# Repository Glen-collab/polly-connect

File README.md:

# 🦜 Polly Connect

**ESP32-based voice assistant for garage/workshop storage management**

Tell Polly where you put things, ask her later. Simple as that.

```
"Hey Polly, the wrench is in the left drawer"
    ... later ...
"Hey Polly, where's my wrench?"
    → "The wrench is in the left drawer"
```

## Architecture

```
┌─────────────────┐         ┌─────────────────┐
│   ESP32 Device  │  WiFi   │   Cloud Server  │
│   (Ears/Mouth)  │◄───────►│    (Brain)      │
│                 │         │                 │
│ • Wake word     │         │ • Whisper STT   │
│ • Audio capture │         │ • Intent parse  │
│ • Audio output  │         │ • Database      │
└─────────────────┘         │ • TTS           │
                            └─────────────────┘
```

**ESP32** handles audio I/O and wake word detection.  
**Server** handles the "smarts" — transcription, understanding, responses.

## Hardware Requirements

| Part | Purpose | ~Price |
|------|---------|--------|
| ESP32-WROOM-32 | Microcontroller | $6 |
| INMP441 | I2S Microphone | $3 |
| MAX98357A | I2S Amplifier | $4 |
| Small Speaker | Audio output | $3 |

**Total: ~$16-20** (vs $100+ for Raspberry Pi build)

## Quick Start

### 1. Server Setup

```bash
cd server

# Create virtual environment
python -m venv venv
source venv/bin/activate  # or `venv\Scripts\activate` on Windows

# Install dependencies
pip install -r requirements.txt

# Run server
python main.py
```

Server runs at `http://localhost:8000`

### 2. ESP32 Setup

1. Install [Arduino IDE](https://www.arduino.cc/en/software)
2. Add ESP32 board support (see [docs/wiring.md](docs/wiring.md))
3. Install libraries:
   - WebSocketsClient
   - ArduinoJson
   - Base64
4. Edit `firmware/polly-esp32/config.h`:
   ```cpp
   #define WIFI_SSID     "your_wifi"
   #define WIFI_PASSWORD "your_password"
   #define SERVER_HOST   "192.168.1.100"  // Your server IP
   ```
5. Upload to ESP32

### 3. Wire It Up

See [docs/wiring.md](docs/wiring.md) for detailed pinout.

Quick reference:
```
INMP441 Mic → ESP32          MAX98357A Amp → ESP32
-----------   -----          -------------   -----
VDD → 3.3V                   VIN → 5V
GND → GND                    GND → GND
SD  → GPIO32                 DIN → GPIO22
WS  → GPIO25                 BCLK → GPIO26
SCK → GPIO33                 LRC → GPIO21
L/R → GND
```

### 4. Test It

1. Open Serial Monitor (115200 baud)
2. Press 'r' to start recording (wake word coming in Phase 4)
3. Speak: "The hammer is on the pegboard"
4. Listen for response

## Project Structure

```
polly-connect/
├── server/                 # Cloud brain (Python/FastAPI)
│   ├── api/                # REST and WebSocket endpoints
│   ├── core/               # Business logic
│   │   ├── intent_parser.py    # NLP command parsing
│   │   ├── database.py         # SQLite storage
│   │   ├── transcription.py    # Whisper STT
│   │   └── tts.py              # Text-to-speech
│   └── main.py             # Entry point
│
├── firmware/               # ESP32 code (Arduino)
│   └── polly-esp32/
│       ├── polly-esp32.ino     # Main sketch
│       ├── config.h            # Configuration
│       ├── audio_capture.h     # Mic driver
│       └── audio_playback.h    # Speaker driver
│
├── wake-word/              # Wake word training assets
│   ├── positive/           # "Hey Polly" samples
│   └── negative/           # Non-wake-word samples
│
└── docs/                   # Documentation
    ├── architecture.md
    ├── wiring.md
    └── api.md
```

## Build Phases

- [x] **Phase 1:** Hardware test (mic + speaker working)
- [ ] **Phase 2:** WiFi streaming (ESP32 → Server)
- [ ] **Phase 3:** Cloud brain (Whisper + intent + TTS)
- [ ] **Phase 4:** Wake word ("Hey Polly")
- [ ] **Phase 5:** Optimization (latency, silence detection)

## Voice Commands

| You say... | Polly does... |
|------------|---------------|
| "The hammer is on the pegboard" | Stores location |
| "Where is the hammer?" | Retrieves location |
| "What's in the red bin?" | Lists items in location |
| "Forget the old screwdriver" | Deletes item |
| "List everything" | Shows all items |

## API

REST API available at `http://localhost:8000/api/`:

```bash
# Natural language command
curl -X POST http://localhost:8000/api/command \
  -H "Content-Type: application/json" \
  -d '{"text": "where is the wrench"}'

# List all items
curl http://localhost:8000/api/items

# Get stats
curl http://localhost:8000/api/stats
```

See [docs/api.md](docs/api.md) for full reference.

## Roadmap

### Polly CONNECT (this repo)
- [x] ESP32 + cloud architecture
- [ ] Full voice pipeline
- [ ] Web dashboard
- [ ] Multi-device support
- [ ] User accounts

### Polly LOCAL (future)
- [ ] Fully offline ESP32-S3 version
- [ ] Limited command vocabulary
- [ ] No cloud required
- [ ] ~$25 total cost

## Credits

Ported from [The Parrot](https://github.com/Glen-collab/parrot) - original Raspberry Pi version.

## License

MIT - Do whatever you want with it.

---

Made for messy garages everywhere. 🔧

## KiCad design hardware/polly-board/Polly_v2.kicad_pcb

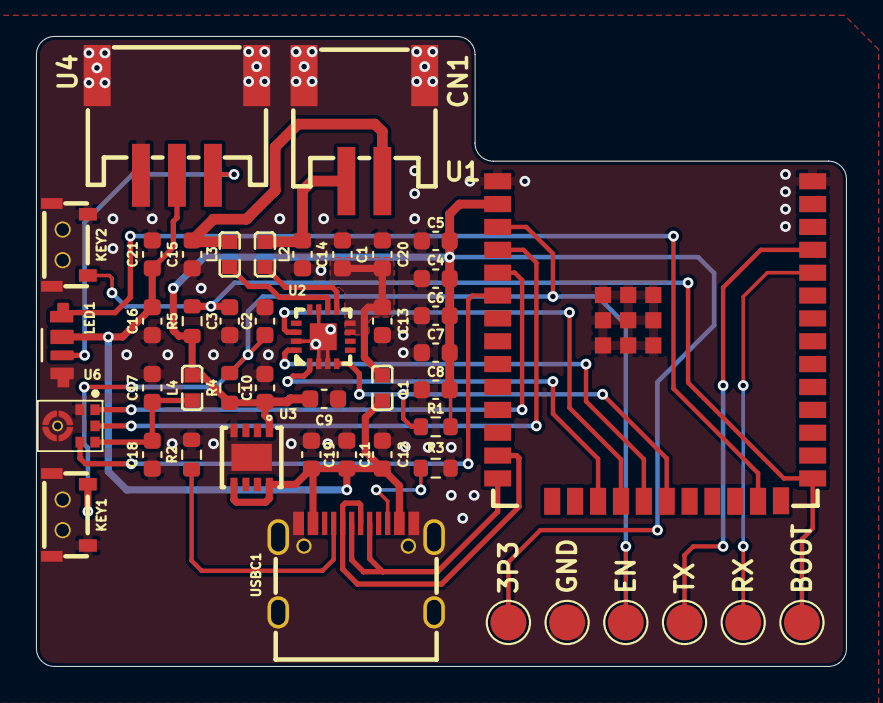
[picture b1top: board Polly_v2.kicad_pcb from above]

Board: 2 copper layers, 45.0 x 35.0 mm, 46 parts (0 on the bottom side), 26 nets.

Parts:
C1, C20: 4.7uF; C_0603_1608Metric
C2, C3, C4, C5, C10, C12, C13, C18, C21: 100nF; C_0603_1608Metric
C6, C7, C8, C9, C11, C17, C19: 10uF; C_0603_1608Metric
C14, C15: 470pF; C_0603_1608Metric
C16: 1uF; C_0603_1608Metric
CN1: S2B-PH-SM4-TB; CONN-SMD_P2.00_S2B-PH-SM4-TB-LF-SN
KEY1, KEY2: SW2; KEY-SMD_1TS003B-2500-3500A-CT
L1, L2, L3, L4: 120Ω@100MHz; L0603
LED1: SK6812SIDE-A-RVS; LED-SMD_4P-L4.0-W1.6-L
R1: 100k; R_0603_1608Metric
R2, R3: 5.1k; R_0603_1608Metric
R4, R5: 10k; R_0603_1608Metric
TP1, TP2, TP3, TP4, TP5, TP6: TestPoint; TestPoint_Pad_D2.0mm
U1: ESP32-S3-WROOM-1; WIRELM-SMD_ESP32-S3-WROOM-1
U2: MAX98357AETE+T; TQFN-16_L3.0-W3.0-P0.50-BL-EP1.5
U3: AP7361-33FGE-7; U-DFN3030-8_L3.0-W3.0-P0.65-BL-EP
U4: S3B-PH-SM4-TB; CONN-SMD_S3B-PH-SM4-TB-LF-SN
U6: ICS-43434_C5656610; MIC-SMD_6P-L3.5-W2.7-P0.90-BL
USBC1: TYPE-C-31-M-12; USB-C_SMD-TYPE-C-31-M-12_1

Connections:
+ESP_3P3: C4.2, C5.2, C6.2, C7.2, C8.2, C9.2, C10.2, L4.1, R1.1, R4.1, R5.1, TP2.1, U1.2 (3V3), U3.1 (OUT)
+MIC_3P3: C17.2, C18.2, L4.2, U6.5 (VDD)
+SP_5P0: C1.2, C13.2, C20.2, L1.2, U2.7 (VDD), U2.8 (VDD)
+USB_5P0: C11.2, C12.2, C16.2, C19.2, C21.2, L1.1, LED1.2 (VDD), U3.5 (EN), U3.8 (IN), U4.2, USBC1.A4B9 (VBUS), USBC1.B4A9 (VBUS)
/ESP_BOOT: C3.1, KEY2.2, R5.2, TP4.1, U1.27 (IO0)
/ESP_EN: C2.1, KEY1.1, R4.2, TP3.1, U1.3 (EN)
/ESP_IO4: U1.4 (IO4), U6.6 (SD)
/ESP_IO5: U1.5 (IO5), U6.1 (WS)
/ESP_IO6: U1.6 (IO6), U6.4 (SCK)
/ESP_IO10: U1.18 (IO10), U2.1 (DIN)
/ESP_IO11: U1.19 (IO11), U2.14 (LRCLK)
/ESP_IO12: U1.20 (IO12), U2.16 (BCLK)
/ESP_IO13: R1.2, U1.21 (IO13), U2.4 (~SD_MODE)
/ESP_IO19: U1.13 (IO19), USBC1.A7 (DN1), USBC1.B7 (DN2)
/ESP_IO20: U1.14 (IO20), USBC1.A6 (DP1), USBC1.B6 (DP2)
/ESP_IO48: LED1.1 (DIN), U1.25 (IO48)
/ESP_RXD0: TP6.1, U1.36 (RXD0)
/ESP_TXD0: TP5.1, U1.37 (TXD0)
GND: C1.1, C2.2, C3.2, C4.1, C5.1, C6.1, C7.1, C8.1, C9.1, C10.1, C11.1, C12.1, C13.1, C14.1, C15.1, C16.1, C17.1, C18.1, C19.1, C20.1, C21.1, CN1.MP, KEY1.0, KEY1.2, KEY2.1, KEY2.MP, LED1.4 (GND), R2.2, R3.2, TP1.1, U1.1 (GND), U1.40 (GND), U1.41 (GND), U2.2 (GAIN_SLOT), U2.3 (GND), U2.11 (GND), U2.15 (GND), U2.17 (EP), U3.4 (GND), U3.9 (GND), U4.3, U4.MP, U6.2 (LR), U6.3 (GND), USBC1.1 (EH), USBC1.2 (EH), USBC1.3 (EH), USBC1.4 (EH), USBC1.A1B12 (GND), USBC1.B1A12 (GND)
unnamed: C14.2, CN1.2, L2.2
unnamed: C15.2, CN1.1, L3.2
unnamed: LED1.3 (DOUT), U4.1
unnamed: L3.1, U2.10 (OUTN)
unnamed: L2.1, U2.9 (OUTP)
unnamed: R2.1, USBC1.A5 (CC1)
unnamed: R3.1, USBC1.B5 (CC2)

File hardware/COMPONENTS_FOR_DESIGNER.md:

# Polly PCB v2 — Canonical Spec

**Source of truth:** `hardware/polly-board/Polly_v2.*` — the KiCad project Paul P. (Upwork) delivered in April 2026.
The schematic, BOM, CPL, and gerbers there are what gets manufactured. This document explains the choices and the
non-negotiable details so a new designer can review or extend the board without re-litigating decisions.

**Board:** 45 × 35 mm, 2-layer FR4, fully SMT-assembled by JLCPCB.

**End-user connections (only these are customer-facing):**
- USB-C (power + firmware flash)
- JST-PH 2-pin SMD (speaker wire out)
- JST-PH 3-pin SMD (LED chain to Polly's eyes)

No exposed pin headers. No hand soldering. UART fallback exposed as **labeled SMD test pads along the bottom edge**
(pogo-pin probe, not a connector).

---

## BOM (Paul's v2, manufactured by JLCPCB)

All part numbers are JLCPCB LCSC codes. Verify stock right before ordering — LCSC parts rotate in and out.

| Ref | Component | LCSC | Package | Notes |
|-----|-----------|------|---------|-------|
| U1 | **ESP32-S3-WROOM-1-N16R8** | **C2913202** | SMD module | **DO NOT SUBSTITUTE.** Must be N16R8 (16 MB flash, 8 MB octal PSRAM). A previous order was substituted to N4R2, which is incompatible with the firmware. Add this as a human-readable order note to JLCPCB. |
| U2 | MAX98357AETE+T | C910544 | TQFN-16 (3×3 mm) | I2S mono audio amp. Runs on **+5V (SP_5V)** for max volume — do NOT tie VDD to +3.3V. **GAIN_SLOT tied to GND = 15 dB (loudest setting).** **SD_MODE controlled by GPIO13** (firmware drives high to enable amp, low to mute — saves power and kills idle hiss). |
| U3 | AP7361-33FGE-7 | C460392 | DFN-8 | 5V → 3.3V LDO regulator, 1 A capability, low noise. Replaces AMS1117 from the v1 spec — better part for clean audio rails. |
| U6 | **ICS-43434** (TDK, I2S MEMS mic) | **C5656610** | LGA-6 | I2S MEMS mic. Replaces MSM261DGT003 (PDM, incompatible with firmware) and INMP441 (out of stock at JLCPCB). 3.3V only (5V will damage the part). |
| LED1 | **SK6812SIDE-A-RVS** | **C2890037** | SMD 4P, side-emit reverse-mount | Addressable RGB, side-firing through a window in the perch / stump wall. Same one-wire 800 kHz protocol as WS2812 — firmware works unchanged. **No series resistor on the data line** (direct GPIO48 → DIN). DOUT chains off-board through the LED-eyes JST. |
| USBC1 | USB-C receptacle (16-pin) | C165948 | TYPE-C-31-M-12 | Power + USB 2.0 data. Place on the **bottom edge** of the board. |
| CN1 | JST-PH 2-pin SMD (speaker out) | **C295747** | S2B-PH-SM4-TB, 2.0 mm pitch, side-entry SMD | Pin 1 = OUTP, Pin 2 = OUTN. SMD = no through-hole soldering at JLCPCB. |
| U4 | JST-PH 3-pin SMD (LED eyes out) | **C265101** | S3B-PH-SM4-TB, 2.0 mm pitch, side-entry SMD | **Pin 1 = DATA (chain-out from LED1 DOUT), Pin 2 = +5V, Pin 3 = GND.** Customer pigtails MUST match this pin order — DATA is on pin 1, not the middle pin. |
| KEY1 | **RESET button** | C255810 | SMD tactile (1TS003B-2500-3500A-CT) | EN → GND when pressed. |
| KEY2 | **BOOT / Story button** | C255810 | SMD tactile (1TS003B-2500-3500A-CT) | GPIO0 → GND when pressed. Doubles as Story button in firmware (short press = record, hold on power-up = flash mode). |

**Passives (all 0603):**

| Ref | Value | LCSC | Purpose |
|-----|-------|------|---------|
| C1, C20 | 4.7 µF | C69335 | USB_5V / SP_5V bulk |
| C10, C12, C13, C18, C2, C21, C3, C4, C5 | 100 nF | C1590 | Decoupling across rails (ESP32, LDO, amp, mic) — including **C2 100nF on EN-to-GND** (RC reset filter) and **C3 100nF on BOOT-to-GND** (debounce) |
| C11, C17, C19, C6, C7, C8, C9 | 10 µF | C70225 | Bulk caps on 3.3V rails and USB VBUS |
| C14, C15 | 470 pF | C1620 | Class-D speaker output EMI filter (paired with L2/L3) |
| C16 | 1 µF | C1592 | LED chain bulk |
| L1, L2, L3, L4 | 120 Ω @ 100 MHz | C14709 | Ferrite beads — **L1 splits USB_5V from SP_5V** (audio gets clean 5V), **L2/L3 on speaker outputs** (Class-D filter), **L4 splits ESP_3V3 from MIC_3V3** (clean mic supply) |
| R1 | 100 kΩ | C14675 | MAX98357A SD_MODE pull-up to GPIO13 |
| R2, R3 | 5.1 kΩ | C14677 | USB-C CC1 / CC2 pull-**downs to GND** |
| R4, R5 | 10 kΩ | C15401 | EN pull-up + BOOT pull-up to +3.3V |

---

## GPIO Pin Assignments (firmware-locked — DO NOT CHANGE)

| GPIO | Function | Connected to |
|------|----------|-------------|
| GPIO0 | BOOT / Story button | KEY2 → GND |
| GPIO4 | Mic SD (I2S data) | U6 SD |
| GPIO5 | Mic WS (I2S word select) | U6 WS |
| GPIO6 | Mic SCK (I2S clock) | U6 SCK |
| GPIO10 | Amp DIN | U2 DIN |
| GPIO11 | Amp LRCLK | U2 LRCLK |
| GPIO12 | Amp BCLK | U2 BCLK |
| **GPIO13** | **Amp SD_MODE (software enable)** | U2 SD_MODE via R1 100k. Firmware must drive HIGH at boot to enable the amp. |
| GPIO19 | USB D- | USBC1 D- |
| GPIO20 | USB D+ | USBC1 D+ |
| GPIO48 | RGB LED data | LED1 DIN |
| EN | Reset | R4 pull-up + KEY1 → GND, with C2 100nF RC filter |

All other GPIOs left floating.

---

## Layout Rules (must match)

See `polly-board/polly_board_v2_final.png` for the visual reference.

1. **Board size: 45 × 35 mm**, 2-layer.
2. **Perch edge** (the edge that faces outward through the 3D-printed stump wall) carries all user-facing components:
   - Left to right: **KEY1 (Reset) — LED1 — U6 (Mic) — KEY2 (Story/BOOT)**
   - **Minimum 15 mm between KEY1 and KEY2** (button cap clearance, ergonomic press)
   - Mic acoustic port faces outward sideways, not down through the PCB
   - LED side-firing through a window in the stump
   - All four components flush with or within 1 mm of the Edge.Cuts boundary
3. **Bottom edge** carries USB-C and six labeled SMD test pads: **3P3, GND, EN, TX, RX, BOOT** (for UART-based firmware recovery via pogo pins).
4. **JSTs (CN1 speaker, U4 LED eyes)** on a non-perch edge — top or back. Wires route internally.
5. **Mic ↔ speaker JST** kept as far apart as the board allows, to reduce acoustic feedback.
6. **ESP32 PCB antenna** overhangs board edge OR has no ground pour / no copper directly beneath it.

---

## Non-negotiable electrical details (don't repeat past mistakes)

- **CC1 and CC2**: 5.1 **kΩ** (NOT 5.1 Ω) pull-**down** to GND (NOT pull-up to 3.3V). USB-C host will refuse to supply power otherwise.
- **USB D+ = GPIO20, USB D- = GPIO19** (native USB).
- **KEY1 (RESET) on EN**, **KEY2 (BOOT) on GPIO0**.
- **R4 (EN pull-up) tied to EN pin** + **C2 100nF on EN-to-GND** for clean reset.
- **ICS-43434 VDD = +3.3V only**. +5V damages it.
- **MAX98357A VDD = +5V (SP_5V via L1 ferrite bead from VBUS)**, NOT +3.3V (quieter at 3.3V).
- **MAX98357A GAIN_SLOT = GND** for 15 dB max gain.
- **MAX98357A SD_MODE = GPIO13 via R1 100k** — firmware must drive HIGH at boot.
- **WS2812 / SK6812 data line direct from GPIO48** — no series resistor.
- **ESP32 module 3V3 pin → +ESP_3P3, GND pins → GND**. Not swapped.
- **Ground pour on both layers**, connected by vias, clear of antenna area.

---

## What to deliver

1. KiCad project (`.kicad_pro`, `.kicad_sch`, `.kicad_pcb`) — already committed at `hardware/polly-board/Polly_v2.*`
2. JLCPCB-ready gerbers (zip) — already at `hardware/polly-board/production/Polly_V2.zip`
3. BOM CSV in LCSC format (`Designator, Footprint, Quantity, Value, LCSC Part #`) — at `hardware/polly-board/production/Polly_V2_bom.csv`
4. CPL / POS CSV (`Designator, Mid X, Mid Y, Rotation, Layer`) — at `hardware/polly-board/production/Polly_V2_positions.csv`

Order quantity: **5–10 prototypes first** for validation before any production run.

---

## Alternate designs in flight

- **Paul P. (Upwork) — `hardware/polly-board/`** — current canonical, manufactured-ready.
- **Fiverr designer (alt) — `hardware/polly-board-alt-fiverr/`** — alternate v2 layout being developed in parallel as a price/quality comparison. Glen plans to assemble both and bench-test before locking in a single design for production.

If you're a new designer joining the project, **start from Paul's files**. If asked to do an "alt" version, copy his project as your starting reference rather than redrawing from scratch.

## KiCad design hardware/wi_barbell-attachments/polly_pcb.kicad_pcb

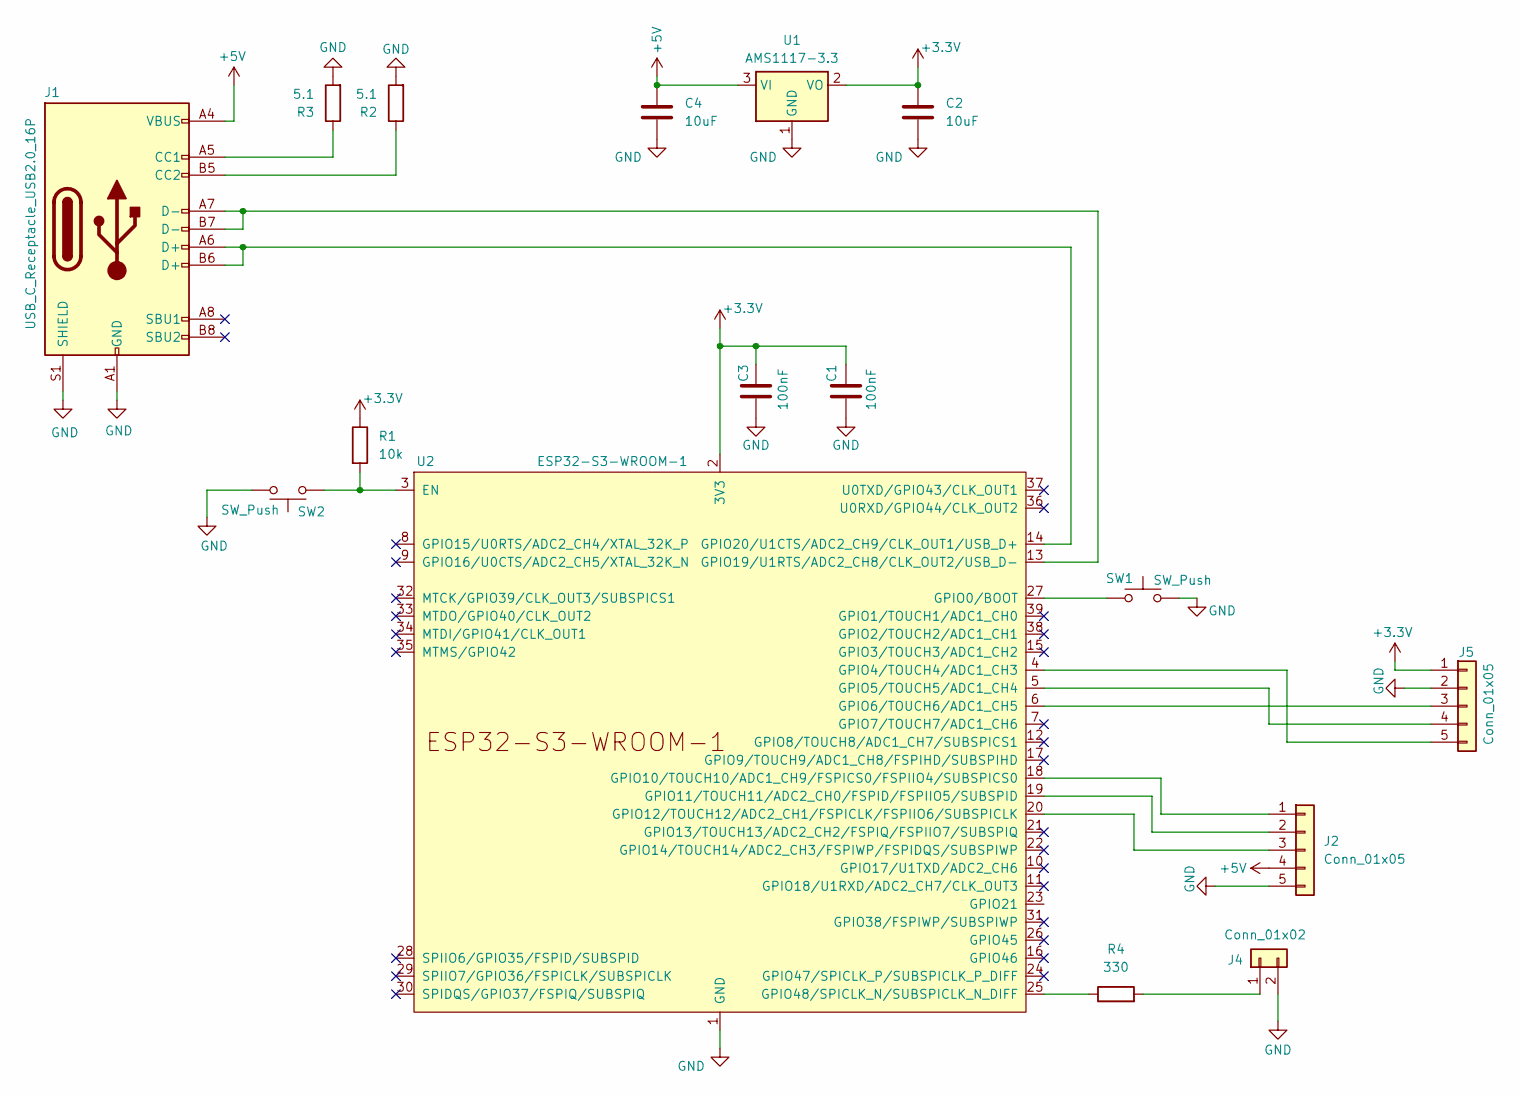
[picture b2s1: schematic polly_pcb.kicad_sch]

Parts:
C1, C3: 100nF; C_0805_2012Metric
C2, C4: 10uF; C_0805_2012Metric
J1: USB_C_Receptacle_USB2.0_16P; USB_C_Receptacle_HRO_TYPE-C-31-M-12
J2, J5: Conn_01x05; PinHeader_1x05_P2.54mm_Vertical
J4: Conn_01x02; PinHeader_1x02_P2.54mm_Vertical
R1: 10k; R_0805_2012Metric
R2, R3: 5.1; R_0805_2012Metric
R4: 330; R_0805_2012Metric
SW1, SW2: SW_Push; SW_SPST_PTS645Sx43SMTR92
U1: AMS1117-3.3; SOT-223-3_TabPin2
U2: ESP32-S3-WROOM-1

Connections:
+3.3V: C1.1, C2.1, C3.1, J5.1, R1.1, U1.2 (VO), U2.2 (3V3)
+5V: C4.1, J1.A4 (VBUS), J1.A9 (VBUS), J1.B4 (VBUS), J1.B9 (VBUS), J2.4, U1.3 (VI)
GND: C1.2, C2.2, C3.2, C4.2, J1.A1 (GND), J1.A12 (GND), J1.B1 (GND), J1.B12 (GND), J1.S1 (SHIELD), J2.5, J4.2, J5.2, R2.2, R3.2, SW1.2, SW2.2, U1.1 (GND), U2.1 (GND), U2.40 (GND), U2.41 (GND)
unnamed: J1.A5 (CC1), R3.1
unnamed: J1.B5 (CC2), R2.1
unnamed: J2.1, U2.18 (GPIO10/TOUCH10/ADC1_CH9/FSPICS0/FSPIIO4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)
unnamed: J2.2, U2.19 (GPIO11/TOUCH11/ADC2_CH0/FSPID/FSPIIO5/S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)
unnamed: J2.3, U2.20 (GPIO12/TOUCH12/ADC2_CH1/FSPICLK/FSPIIO6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)
unnamed: J4.1, R4.2
unnamed: J5.3, U2.6 (GPIO6/TOUCH6/ADC1_CH5)
unnamed: J5.4, U2.5 (GPIO5/TOUCH5/ADC1_CH4)
unnamed: J5.5, U2.4 (GPIO4/TOUCH4/ADC1_CH3)
unnamed: R1.2, SW2.1, U2.3 (EN)
unnamed: SW1.1, U2.27 (GPIO0/BOOT)
unnamed: J1.A7 (D-), J1.B7 (D-), U2.13 (GPIO19/U1RTS/ADC2_CH8/CLK_OUT2/USB_D-)
unnamed: J1.A6 (D+), J1.B6 (D+), U2.14 (GPIO20/U1CTS/ADC2_CH9/CLK_OUT1/USB_D+)
unnamed: R4.1, U2.25 (GPIO48/SPICLK_N/SUBSPICLK_N_DIFF)

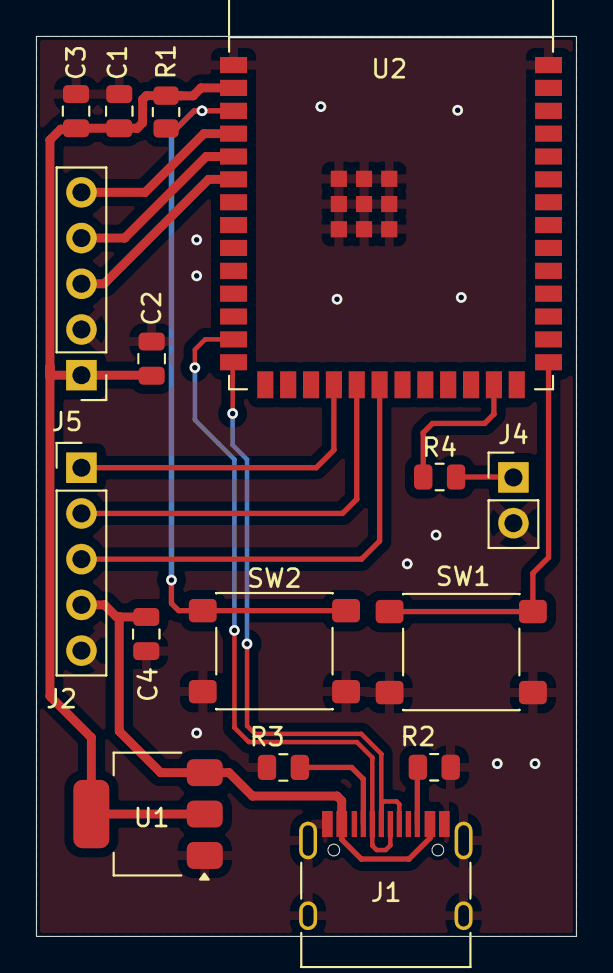
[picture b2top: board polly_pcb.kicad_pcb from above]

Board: 2 copper layers, 30.0 x 50.0 mm, 16 parts (0 on the bottom side), 17 nets.

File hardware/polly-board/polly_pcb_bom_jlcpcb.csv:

Comment,Designator,Footprint,LCSC
100nF,"C1,C3",C_0805_2012Metric,C49678
10uF,"C2,C4",C_0805_2012Metric,C15850
USB_C_Receptacle_USB2.0_16P,J1,USB_C_Receptacle_HRO_TYPE-C-31-M-12,C165948
Conn_01x05,"J2,J5",PinHeader_1x05_P2.54mm_Vertical,C358687
Conn_01x02,J4,PinHeader_1x02_P2.54mm_Vertical,C376042
10k,R1,R_0805_2012Metric,C17414
5.1k,"R2,R3",R_0805_2012Metric,C27834
330,R4,R_0805_2012Metric,C23138
SW_Push,"SW1,SW2",SW_SPST_PTS645Sx43SMTR92,C221880
AMS1117-3.3,U1,SOT-223-3_TabPin2,C6186
ESP32-S3-WROOM-1-N16R8,U2,ESP32-S3-WROOM-1,C2913202

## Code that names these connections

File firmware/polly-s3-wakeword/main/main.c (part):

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 *   7. ESP32 plays TTS audio, resumes streaming
 *
 * GPIO Wiring (INMP441):
 *   SCK  -> GPIO6
 *   WS   -> GPIO5
 *   SD   -> GPIO4
 *   L/R  -> GND (left channel)
 *   VDD  -> 3.3V
 *   GND  -> GND
 *
 * GPIO Wiring (MAX98357A speaker amp):
 *   BCLK -> GPIO12
 *   LRC  -> GPIO11
 *   DIN  -> GPIO10
 *   VIN  -> 5V
 *   GND  -> GND
 */
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// Status LED (built-in on most S3 devkits)
#define LED_PIN         GPIO_NUM_48

// Story mode button (GPIO0 = BOOT button, free during runtime)
#define STORY_BUTTON    GPIO_NUM_0
#define DEBOUNCE_MS     300

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#define MSG_ACCUM_SIZE  32768       // 32KB


/* --- RGB LED (WS2812 on GPIO48) --- */

static led_strip_handle_t led_strip = NULL;

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}


/* --- Story Button (GPIO0 / BOOT) --- */

static void IRAM_ATTR story_button_isr(void *arg)
{
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
static void wifi_provision_init(void)
{
    // Check if GPIO0 (BOOT button) is held at startup = force provisioning
    gpio_config_t btn_check = {
        .pin_bit_mask = (1ULL << GPIO_NUM_0),
        .mode = GPIO_MODE_INPUT,
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
    // Init WiFi (with provisioning — checks NVS, fallback to AP captive portal)
    // Note: story_button_init() moved AFTER wifi because wifi_provision_init
    // reads GPIO0 for force-provisioning before ISR is installed
    wifi_provision_init();

    // Init story button (after WiFi so GPIO0 check for provisioning works)
    story_button_init();

    // Allocate response audio buffer in PSRAM
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
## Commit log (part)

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2026-03-22 Restore working medications template
2026-03-22 Test: change only h1 text to Reminders
2026-03-22 Fix: add w-full to header flex container for mobile width
2026-03-22 Test: wrap all content in width:100% div
2026-03-22 Test: obvious text change to verify caching
2026-03-22 Rename to Daily Reminders (longer text prevents mobile flex collapse)
2026-03-22 Fix: wrap content in min-w-full div to force full width on mobile
2026-03-22 Fix: add w-full to main tag - flex child was shrinking to content width
2026-04-22 Fix CSRF white page when opening installed PWA
    Service worker was caching /web/login, so installed PWAs could serve a
    stale login page whose baked-in CSRF token no longer matched the current
    session cookie — submitting the form returned a bare 403 "CSRF validation
    failed" body (the white page). Three changes:
    - sw.js: skip caching auth pages entirely; bump cache to polly-v3 so
    existing clients purge the old stale login on activate.
2026-04-24 Update PCB v2 spec to match Paul's finalized design (Apr 2026)
    Rewrite hardware/PCB_V2_SPEC.md so a fresh designer picking up the
    manufacturing-file work has the current truth, not the Fiverr-era spec.
    Changes from Paul's Upwork handoff:
    - Mic: INMP441 → ICS-43434 (INMP441 out of stock at JLCPCB; ICS-43434
    is drop-in I2S compatible with the firmware's SCK/WS/SD pinout)
    - Board size: 70×50 mm → 36×45 mm
2026-04-24 Archive Paul's final board render + fix spec to match
    Add hardware/polly-board/polly_board_v2_final.png (the image Paul posted
    April 16 and Glen approved April 17) so the next designer has the visual
    reference alongside the written spec.
    Corrections from the render:
    - Board size is 45 x 35 mm, not the 36 x 45 mm mentioned in Paul's Apr 14
    intermediate message. Paul tightened it further in the final revision.
2026-04-24 Add one-page components handoff for new designer
    Extract just the parts list + critical layout rules from PCB_V2_SPEC.md
    into a single focused document the new designer can build from without
    needing Paul's KiCad files.
    Includes:
    - BOM with LCSC part numbers (mic flagged for verify-at-order-time)
    - GPIO pin assignments from the working breadboard
